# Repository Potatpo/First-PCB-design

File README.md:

# First PCB design
 This is my first attempt at a 65% layout pcb with support for oled and a rotary encoder.

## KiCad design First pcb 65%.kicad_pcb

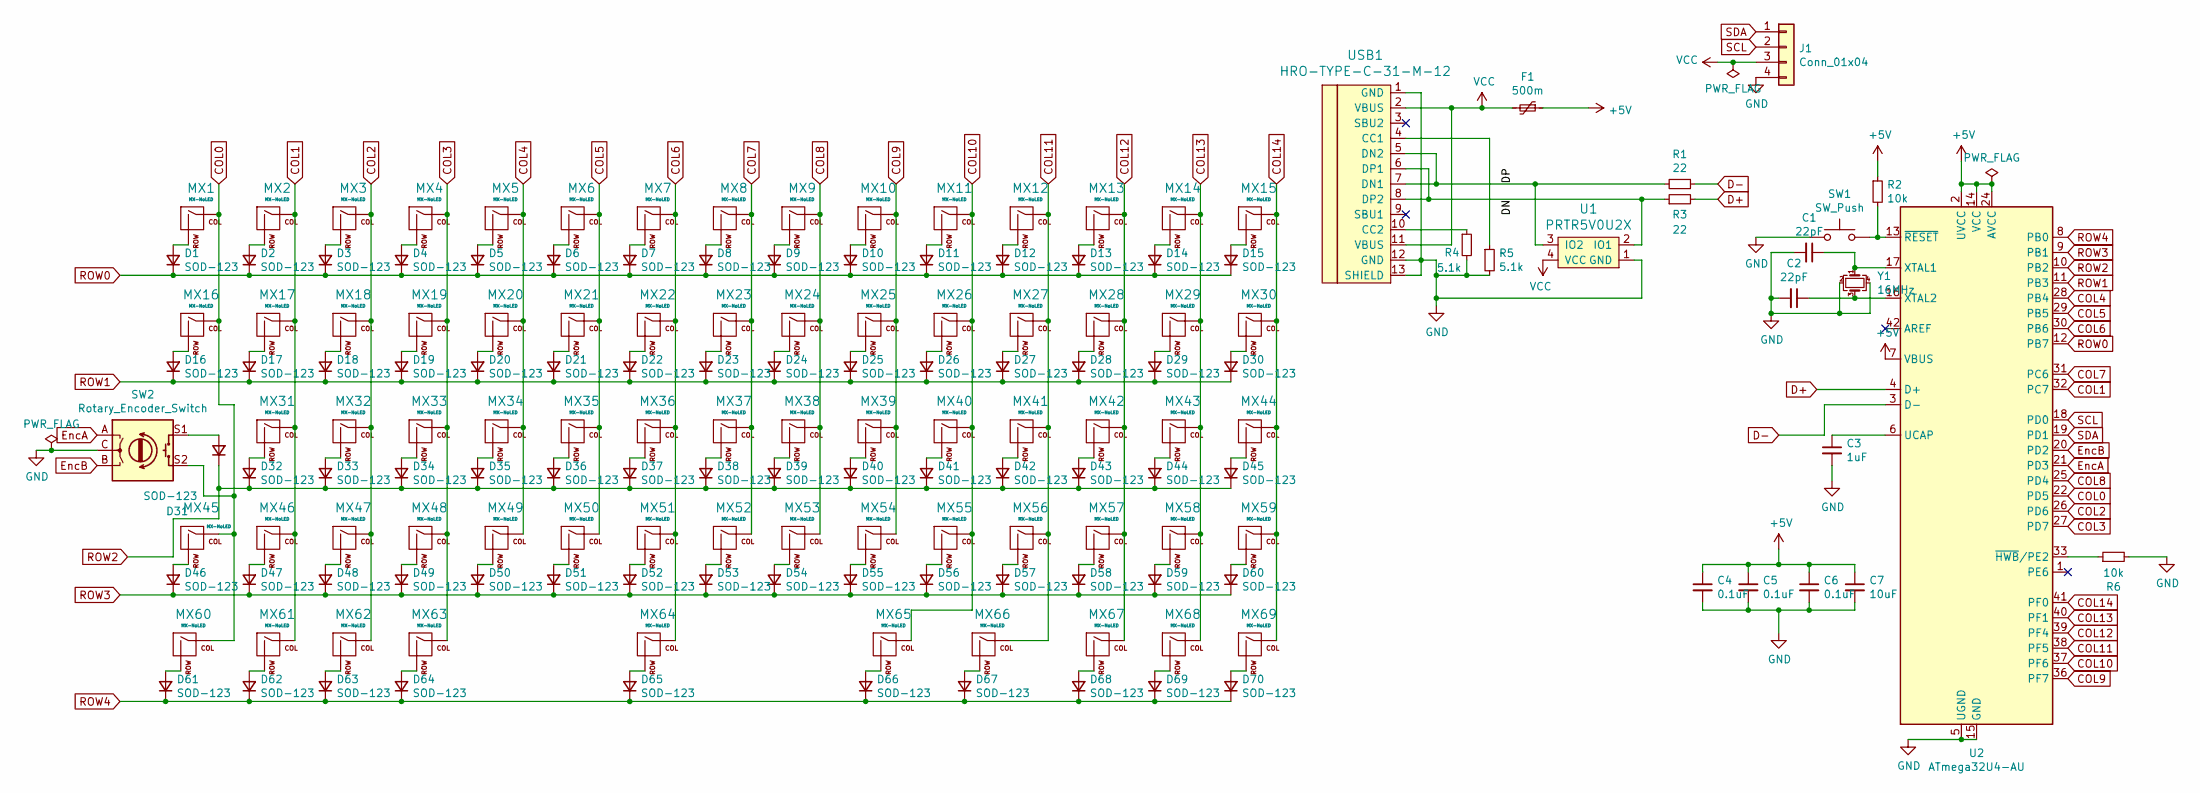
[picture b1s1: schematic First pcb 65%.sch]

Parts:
C1, C2: 22pF; C_0805_2012Metric
C3: 1uF; C_0805_2012Metric
C4, C5, C6: 0.1uF; C_0805_2012Metric
C7: 10uF; C_0805_2012Metric
D1, D2, D3, D4, D5, D6, D7, D8, D9, D10, D11, D12, D13, D14, D15, D16, D17, D18, D19, D20, D21, D22, D23, D24, D25, D26, D27, D28, D29, D30, D31, D32, D33, D34, D35, D36, D37, D38, D39, D40, D41, D42, D43, D44, D45, D46, D47, D48, D49, D50, D51, D52, D53, D54, D55, D56, D57, D58, D59, D60, D61, D62, D63, D64, D65, D66, D67, D68, D69, D70: SOD-123; D_SOD-123
F1: 500m; Fuse_1206_3216Metric
J1: Conn_01x04; 128x64OLED
MX1, MX2, MX3, MX4, MX5, MX6, MX7, MX8, MX9, MX10, MX11, MX12, MX13, MX15, MX17, MX18, MX19, MX20, MX21, MX22, MX23, MX24, MX25, MX26, MX27, MX28, MX30, MX32, MX33, MX34, MX35, MX36, MX37, MX38, MX39, MX40, MX41, MX42, MX44, MX45, MX47, MX48, MX49, MX50, MX51, MX52, MX53, MX54, MX55, MX56, MX58, MX59, MX60, MX67, MX68, MX69: MX-NoLED; MXOnly-1U-NoLED
MX14: MX-NoLED; MXOnly-2U-NoLED
MX16, MX29: MX-NoLED; MXOnly-1.5U-NoLED
MX31, MX57: MX-NoLED; MXOnly-1.75U-NoLED
MX43, MX46: MX-NoLED; MXOnly-2.25U-NoLED
MX61, MX62, MX63, MX65, MX66: MX-NoLED; MXOnly-1.25U-NoLED
MX64: MX-NoLED; MXOnly-6.25U-NoLED
R1, R3: 22; R_0805_2012Metric
R2, R6: 10k; R_0805_2012Metric
R4, R5: 5.1k; R_0805_2012Metric
SW1: SW_Push; SW_SPST_SKQG_WithStem
SW2: Rotary_Encoder_Switch; RotaryEncoder_Alps_EC11E-Switch_Vertical_H20mm
U1: PRTR5V0U2X; SOT143B
U2: ATmega32U4-AU; TQFP-44_10x10mm_P0.8mm
USB1: HRO-TYPE-C-31-M-12; HRO-TYPE-C-31-M-12-HandSoldering
Y1: 16MHz; Crystal_SMD_3225-4Pin_3.2x2.5mm

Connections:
+5V: C4.1, C5.1, C6.1, C7.1, F1.1, R2.1, U2.2 (UVCC), U2.7 (VBUS), U2.14 (VCC), U2.24 (AVCC), U2.34 (VCC), U2.44 (AVCC)
/DN: R3.1, U1.2 (IO1), USB1.6 (DP1), USB1.8 (DP2)
/DP: R1.2, U1.3 (IO2), USB1.5 (DN2), USB1.7 (DN1)
COL0: MX1.1 (COL), MX16.1 (COL), MX45.1 (COL), MX60.1 (COL), SW2.S2, U2.22 (PD5)
COL1: MX2.1 (COL), MX17.1 (COL), MX31.1 (COL), MX46.1 (COL), MX61.1 (COL), U2.32 (PC7)
COL2: MX3.1 (COL), MX18.1 (COL), MX32.1 (COL), MX47.1 (COL), MX62.1 (COL), U2.26 (PD6)
COL3: MX4.1 (COL), MX19.1 (COL), MX33.1 (COL), MX48.1 (COL), MX63.1 (COL), U2.27 (PD7)
COL4: MX5.1 (COL), MX20.1 (COL), MX34.1 (COL), MX49.1 (COL), U2.28 (PB4)
COL5: MX6.1 (COL), MX21.1 (COL), MX35.1 (COL), MX50.1 (COL), U2.29 (PB5)
COL6: MX7.1 (COL), MX22.1 (COL), MX36.1 (COL), MX51.1 (COL), MX64.1 (COL), U2.30 (PB6)
COL7: MX8.1 (COL), MX23.1 (COL), MX37.1 (COL), MX52.1 (COL), U2.31 (PC6)
COL8: MX9.1 (COL), MX24.1 (COL), MX38.1 (COL), MX53.1 (COL), U2.25 (PD4)
COL9: MX10.1 (COL), MX25.1 (COL), MX39.1 (COL), MX54.1 (COL), U2.36 (PF7)
COL10: MX11.1 (COL), MX26.1 (COL), MX40.1 (COL), MX55.1 (COL), MX65.1 (COL), U2.37 (PF6)
COL11: MX12.1 (COL), MX27.1 (COL), MX41.1 (COL), MX56.1 (COL), MX66.1 (COL), U2.38 (PF5)
COL12: MX13.1 (COL), MX28.1 (COL), MX42.1 (COL), MX57.1 (COL), MX67.1 (COL), U2.39 (PF4)
COL13: MX14.1 (COL), MX29.1 (COL), MX43.1 (COL), MX58.1 (COL), MX68.1 (COL), U2.40 (PF1)
COL14: MX15.1 (COL), MX30.1 (COL), MX44.1 (COL), MX59.1 (COL), MX69.1 (COL), U2.41 (PF0)
D+: R3.2, U2.4 (D+)
D-: R1.1, U2.3 (D-)
EncA: SW2.A, U2.21 (PD3)
EncB: SW2.B, U2.20 (PD2)
GND: C1.2, C2.2, C3.2, C4.2, C5.2, C6.2, C7.2, J1.4, R4.2, R5.2, R6.2, SW1.1, SW2.C, U1.1 (GND), U2.5 (UGND), U2.15 (GND), U2.23 (GND), U2.35 (GND), U2.43 (GND), USB1.1 (GND), USB1.12 (GND), USB1.13 (SHIELD), Y1.2, Y1.4
unnamed: C1.1, U2.17 (XTAL1), Y1.1
unnamed: C2.1, U2.16 (XTAL2), Y1.3
unnamed: C3.1, U2.6 (UCAP)
unnamed: D1.2 (A), MX1.2 (ROW)
unnamed: D2.2 (A), MX2.2 (ROW)
unnamed: D3.2 (A), MX3.2 (ROW)
unnamed: D4.2 (A), MX4.2 (ROW)
unnamed: D5.2 (A), MX5.2 (ROW)
unnamed: D6.2 (A), MX6.2 (ROW)
unnamed: D7.2 (A), MX7.2 (ROW)
unnamed: D8.2 (A), MX8.2 (ROW)
unnamed: D9.2 (A), MX9.2 (ROW)
unnamed: D10.2 (A), MX10.2 (ROW)
unnamed: D11.2 (A), MX11.2 (ROW)
unnamed: D12.2 (A), MX12.2 (ROW)
unnamed: D13.2 (A), MX13.2 (ROW)
unnamed: D14.2 (A), MX14.2 (ROW)
unnamed: D15.2 (A), MX15.2 (ROW)
unnamed: D16.2 (A), MX16.2 (ROW)
unnamed: D17.2 (A), MX17.2 (ROW)
unnamed: D18.2 (A), MX18.2 (ROW)
unnamed: D19.2 (A), MX19.2 (ROW)
unnamed: D20.2 (A), MX20.2 (ROW)
unnamed: D21.2 (A), MX21.2 (ROW)
unnamed: D22.2 (A), MX22.2 (ROW)
unnamed: D23.2 (A), MX23.2 (ROW)
unnamed: D24.2 (A), MX24.2 (ROW)
unnamed: D25.2 (A), MX25.2 (ROW)
unnamed: D26.2 (A), MX26.2 (ROW)
unnamed: D27.2 (A), MX27.2 (ROW)
unnamed: D28.2 (A), MX28.2 (ROW)
unnamed: D29.2 (A), MX29.2 (ROW)
unnamed: D30.2 (A), MX30.2 (ROW)
unnamed: D31.2 (A), SW2.S1
unnamed: D32.2 (A), MX31.2 (ROW)
unnamed: D33.2 (A), MX32.2 (ROW)
unnamed: D34.2 (A), MX33.2 (ROW)
unnamed: D35.2 (A), MX34.2 (ROW)
unnamed: D36.2 (A), MX35.2 (ROW)
unnamed: D37.2 (A), MX36.2 (ROW)
unnamed: D38.2 (A), MX37.2 (ROW)
unnamed: D39.2 (A), MX38.2 (ROW)
unnamed: D40.2 (A), MX39.2 (ROW)
unnamed: D41.2 (A), MX40.2 (ROW)
unnamed: D42.2 (A), MX41.2 (ROW)
unnamed: D43.2 (A), MX42.2 (ROW)
unnamed: D44.2 (A), MX43.2 (ROW)
unnamed: D45.2 (A), MX44.2 (ROW)
unnamed: D46.2 (A), MX45.2 (ROW)
unnamed: D47.2 (A), MX46.2 (ROW)
unnamed: D48.2 (A), MX47.2 (ROW)
unnamed: D49.2 (A), MX48.2 (ROW)
unnamed: D50.2 (A), MX49.2 (ROW)
unnamed: D51.2 (A), MX50.2 (ROW)
unnamed: D52.2 (A), MX51.2 (ROW)
unnamed: D53.2 (A), MX52.2 (ROW)
unnamed: D54.2 (A), MX53.2 (ROW)
unnamed: D55.2 (A), MX54.2 (ROW)
unnamed: D56.2 (A), MX55.2 (ROW)
unnamed: D57.2 (A), MX56.2 (ROW)
unnamed: D58.2 (A), MX57.2 (ROW)
unnamed: D59.2 (A), MX58.2 (ROW)
unnamed: D60.2 (A), MX59.2 (ROW)
unnamed: D61.2 (A), MX60.2 (ROW)
unnamed: D62.2 (A), MX61.2 (ROW)
unnamed: D63.2 (A), MX62.2 (ROW)
unnamed: D64.2 (A), MX63.2 (ROW)
unnamed: D65.2 (A), MX64.2 (ROW)
unnamed: D66.2 (A), MX65.2 (ROW)
unnamed: D67.2 (A), MX66.2 (ROW)
unnamed: D68.2 (A), MX67.2 (ROW)
unnamed: D69.2 (A), MX68.2 (ROW)
unnamed: D70.2 (A), MX69.2 (ROW)
unnamed: R2.2, SW1.2, U2.13 (~RESET)
unnamed: R4.1, USB1.10 (CC2)
unnamed: R5.1, USB1.4 (CC1)
unnamed: R6.1, U2.33 (~HWB~/PE2)
ROW0: D1.1 (K), D2.1 (K), D3.1 (K), D4.1 (K), D5.1 (K), D6.1 (K), D7.1 (K), D8.1 (K), D9.1 (K), D10.1 (K), D11.1 (K), D12.1 (K), D13.1 (K), D14.1 (K), D15.1 (K), U2.12 (PB7)
ROW1: D16.1 (K), D17.1 (K), D18.1 (K), D19.1 (K), D20.1 (K), D21.1 (K), D22.1 (K), D23.1 (K), D24.1 (K), D25.1 (K), D26.1 (K), D27.1 (K), D28.1 (K), D29.1 (K), D30.1 (K), U2.11 (PB3)
ROW2: D31.1 (K), D32.1 (K), D33.1 (K), D34.1 (K), D35.1 (K), D36.1 (K), D37.1 (K), D38.1 (K), D39.1 (K), D40.1 (K), D41.1 (K), D42.1 (K), D43.1 (K), D44.1 (K), D45.1 (K), U2.10 (PB2)
ROW3: D46.1 (K), D47.1 (K), D48.1 (K), D49.1 (K), D50.1 (K), D51.1 (K), D52.1 (K), D53.1 (K), D54.1 (K), D55.1 (K), D56.1 (K), D57.1 (K), D58.1 (K), D59.1 (K), D60.1 (K), U2.9 (PB1)
ROW4: D61.1 (K), D62.1 (K), D63.1 (K), D64.1 (K), D65.1 (K), D66.1 (K), D67.1 (K), D68.1 (K), D69.1 (K), D70.1 (K), U2.8 (PB0)
SCL: J1.2, U2.18 (PD0)
SDA: J1.1, U2.19 (PD1)
VCC: F1.2, J1.3, U1.4 (VCC), USB1.2 (VBUS), USB1.11 (VBUS)

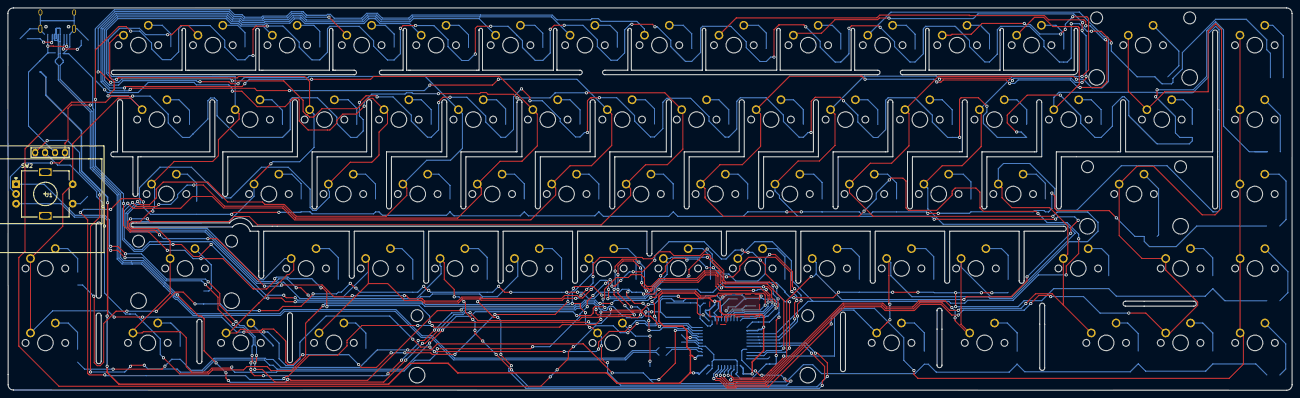
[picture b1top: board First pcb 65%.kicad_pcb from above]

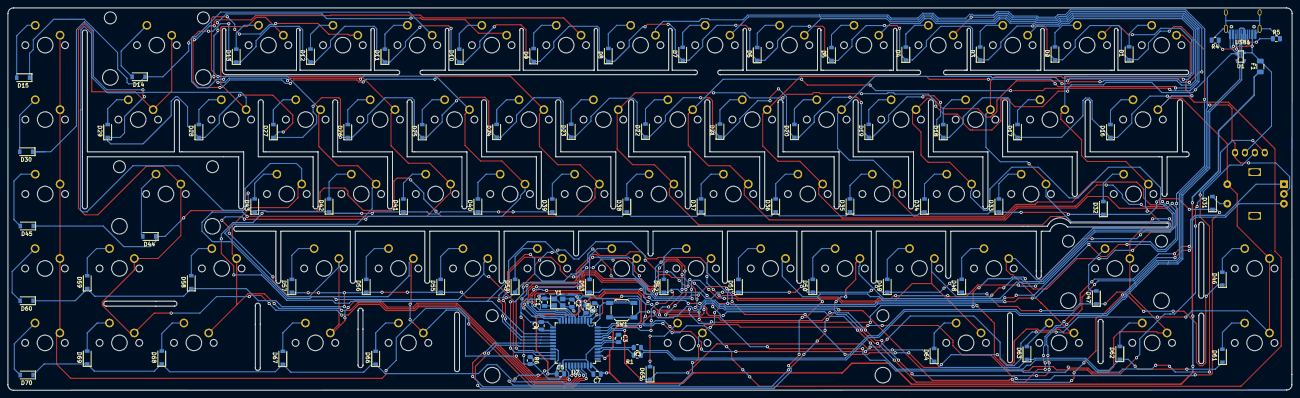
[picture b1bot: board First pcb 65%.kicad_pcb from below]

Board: 2 copper layers, 328.7 x 97.9 mm, 160 parts (89 on the bottom side), 108 nets.

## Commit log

2021-09-16 65% keyboard pcb
    This is my attempt at a 65% pcb with a rotary encoder and oled. This is also my first ever time making a pcb lol.
2021-09-16 Add submodules
2021-09-16 added libraries
2021-09-18 pcb stuff
2021-09-19 added plate file and pcb progress
2021-09-19 more libraries
2021-09-20 https://github.com/keebio/Keebio-Parts.pretty
2021-09-20 added i2c library and added footprints
2021-09-24 pcb updates
2021-10-15 routing
